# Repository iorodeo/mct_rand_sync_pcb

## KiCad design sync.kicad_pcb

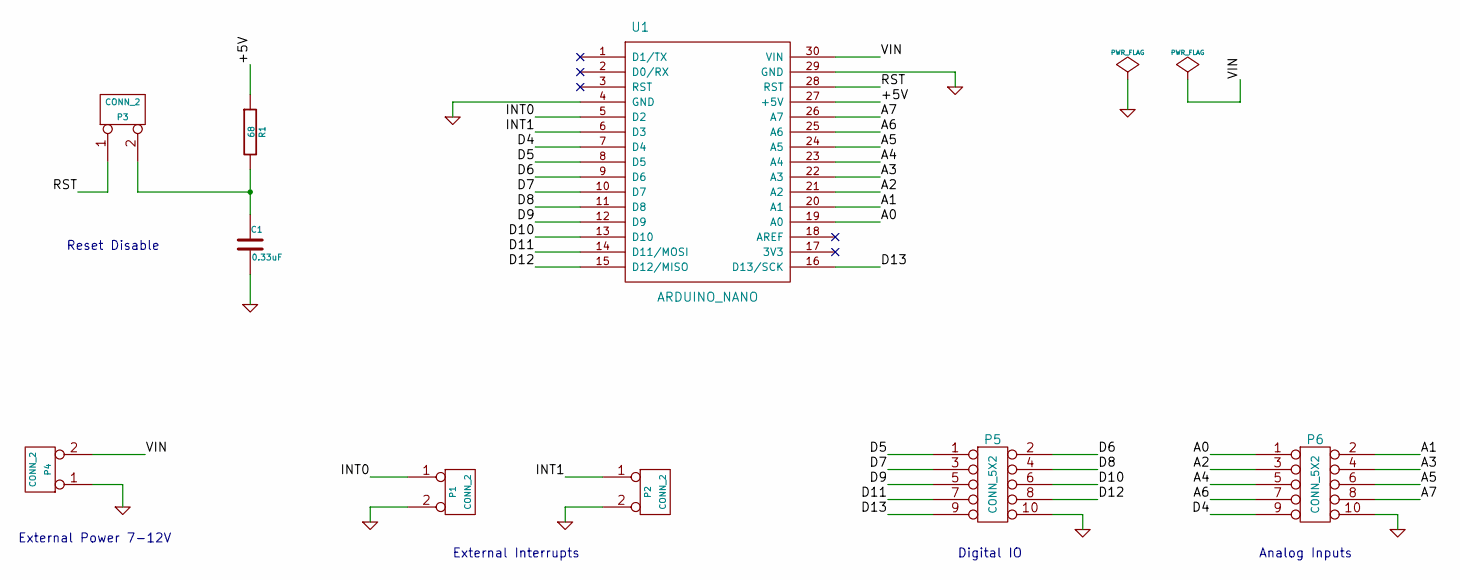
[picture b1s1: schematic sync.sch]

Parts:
C1: 0.33uF
P1, P2, P3, P4: CONN_2
P5, P6: CONN_5X2
R1: 68
U1: ARDUINO_NANO

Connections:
/+5V: R1.1, U1.27 (+5V)
/A0: P6.1, U1.19 (A0)
/A1: P6.2, U1.20 (A1)
/A2: P6.3, U1.21 (A2)
/A3: P6.4, U1.22 (A3)
/A4: P6.5, U1.23 (A4)
/A5: P6.6, U1.24 (A5)
/A6: P6.7, U1.25 (A6)
/A7: P6.8, U1.26 (A7)
/D4: P6.9, U1.7 (D4)
/D5: P5.1, U1.8 (D5)
/D6: P5.2, U1.9 (D6)
/D7: P5.3, U1.10 (D7)
/D8: P5.4, U1.11 (D8)
/D9: P5.5, U1.12 (D9)
/D10: P5.6, U1.13 (D10)
/D11: P5.7, U1.14 (D11/MOSI)
/D12: P5.8, U1.15 (D12/MISO)
/D13: P5.9, U1.16 (D13/SCK)
/INT0: P1.1, U1.5 (D2)
/INT1: P2.1, U1.6 (D3)
/RST: P3.1, U1.28 (RST)
/VIN: P4.2 (PM), U1.30 (VIN)
GND: C1.2, P1.2 (PM), P2.2 (PM), P4.1, P5.10, P6.10, U1.4 (GND), U1.29 (GND)
unnamed: C1.1, P3.2 (PM), R1.2

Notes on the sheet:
External Power 7-12V
External Interrupts
Digital IO
Analog Inputs
Reset Disable

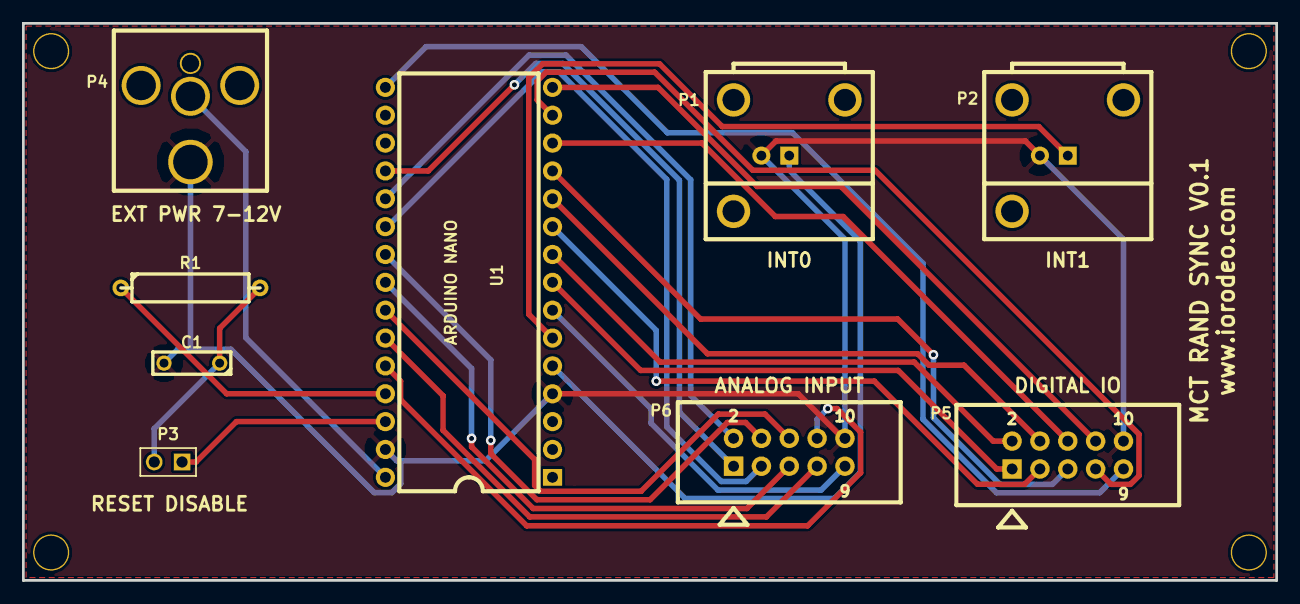
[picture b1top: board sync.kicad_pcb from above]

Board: 2 copper layers, 114.3 x 50.8 mm, 13 parts (0 on the bottom side), 25 nets.

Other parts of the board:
M1, M2, M3, M4: VAL**; MOUNT_HOLE_4_40

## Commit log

2013-10-28 Project creation.
2013-11-02 Added v0.1 gerber files.
2013-11-05 Rearranged schematic.
